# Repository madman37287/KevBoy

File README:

What is the KevBoy?

In its current state, the KevBoy is a breadboard prototype of a handheld RPI based retro gaming system using the retropie image.
ADD IMAGE

The KevBoy is a 

What is the purpose of making this public git repository?

1. Back-up data.  This project already had to be re-designed from scratch once in the past due to a laptop harddrive failure.  
2. Some SW and HW lack a large number of examples or documentation on the web. I hope this repository and documentation can assist with someone else's learning.
3. Method of showing off the project to any interested parties.

What has already been implemented within the KevBoy?

As previously mentioned, the KevBoy currently has a breadboard prototype shown in the image below.
ADD IMAGE

The breadboard design has 3 visible layers to it.  In the bottom layer, we have the controls.
These controls match what you would expect from a standard controller:
* D-Pad on the far left
* A, B, X, Y buttons on the far right
* Two analog sticks
* select (left) and start (right) buttons in between the analog sticks.

INSERT DIAGRAM

There is also an MCP3008 ADC between the analog sticks that convert the analog voltage outputted from the x and y axis potentiometers into a digital code readable by the PI.

The layer above the controls lives the necessary electrical components needed to connect the controls to the GPIO pins.  
In this layer we have LEDs acting only as Diodes.  These diodes are necessary due to the button matrix solution used to reduce the number of GPIO pins used from 16 to 8.
Without the diodes, multiple button presses can lead to an unpressed button being incorrectly registered (see below)

INSERT DIAGRAM

In its current prototype state, the PI currently has 11 connected buttons (including L3 on the DS3 analog), while the final will support at least 16 when adding R3 and the Triggers.
With several other devices needing to be connected to the GPIO pins, such as ADC, PWM speakers, UPS UART connections, ect, there are simply not enough pins.
The HW/SW solution was to build a button matrix, in which 16 buttons could be supported with 8 pins.

What still needs to be implemented?

* Upgrade to RPI5 (expecting CM5 to release later this year. CM4 to CM5 will not require PCB changes)
* Battery solution for RPI5 (5V 5A max compared to RPI4 5V 3A)
* PCB updates & PCB prototype
* 3D printable model for casing
* digitally controllable potentiometers for volume control
* code to support WIFI and Bluetooth status display. Perhaps also an airplane mode.
* Unit cooling

Setup:

Sound:
https://learn.adafruit.com/adafruit-max98357-i2s-class-d-mono-amp/raspberry-pi-usage

Background music: 
https://github.com/Naprosnia/RetroPie_BGM_Player

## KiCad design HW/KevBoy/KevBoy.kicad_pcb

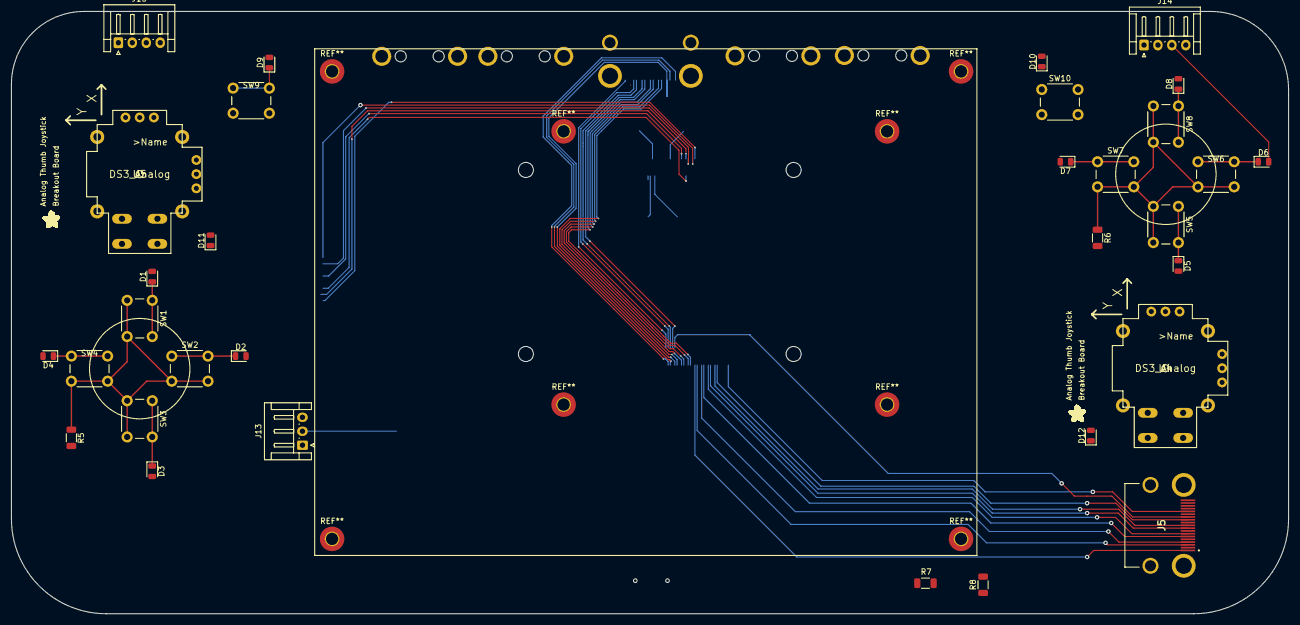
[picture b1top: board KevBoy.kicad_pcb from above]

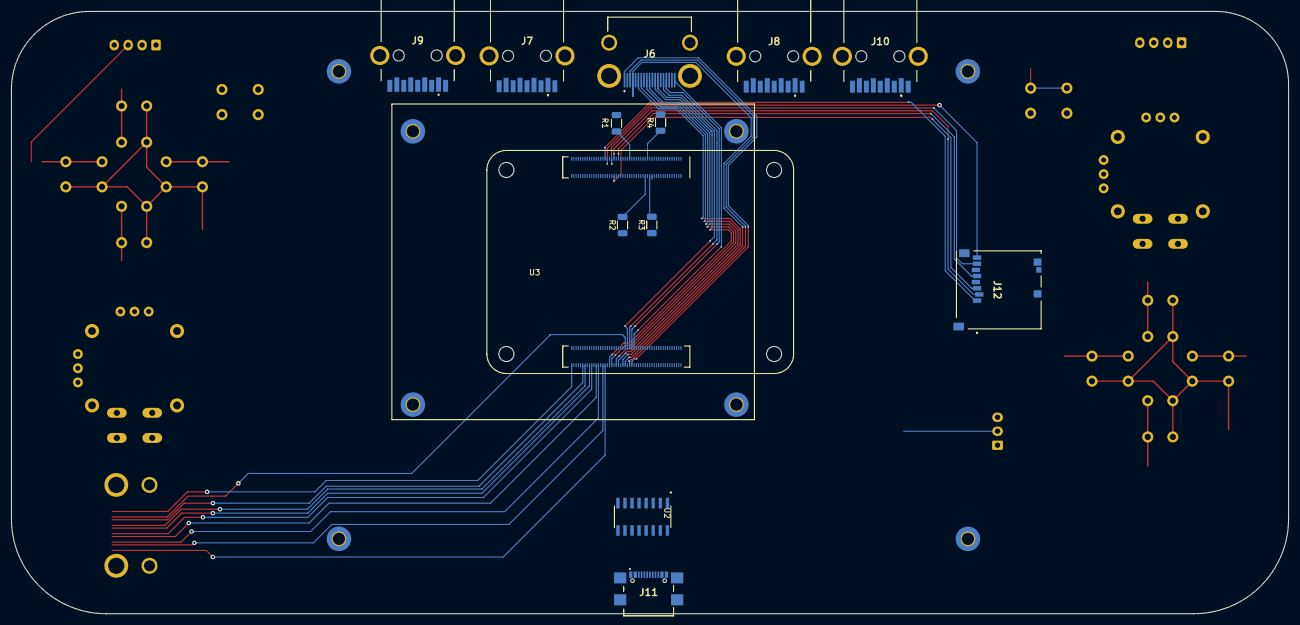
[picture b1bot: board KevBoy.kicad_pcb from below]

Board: 2 copper layers, 229.0 x 108.0 mm, 47 parts (13 on the bottom side), 58 nets.

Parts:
D1, D2, D3, D4, D5, D6, D7, D8, D9, D10, D11, D12: DIODE; D_0805_2012Metric
J5, J6: 208658-1051; 2086581051
J7, J8, J9, J10: 692122030100
J11: USB4110-GF-A; USB4110GFA
J12: MEM2051-00-195-00-A; MEM20510019500A
J13: Conn_01x03; JST_EH_S3B-EH_1x03_P2.50mm_Horizontal
J14, J15: Conn_01x04; JST_EH_S4B-EH_1x04_P2.50mm_Horizontal
R1, R2, R3, R4: 470; R_1206_3216Metric
R5, R6, R7, R8: 10k; R_1206_3216Metric
SW1, SW2, SW3, SW4, SW5, SW6, SW7, SW8, SW9, SW10: SW_Push; SW_PUSH_6mm_H7.3mm
U2: MCP3008; SOIC127P600X175-16N
U3: cm4conn; Raspberry-Pi-4-Compute-Module
U4, U5: DS3_Analog; JOYSTICK
U$1, U$1#2: ADAFRUIT200MIL

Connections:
5V: J13.1, U3.77, U3.79, U3.81, U3.83, U3.85, U3.87
ChargerInput: J11.A4, J11.A9, J11.B4, J11.B9
GND: J11.A1, J11.A12, J11.B1, J11.B12, J12.P6 (VSS), J13.3, R5.2, R6.2, R7.2, R8.2, U2.9 (DGND), U2.14 (AGND), U3.1, U3.2, U3.7, U3.8, U3.13, U3.14, U3.22, U3.23, U3.32, U3.33, U3.42, U3.43, U3.52, U3.53, U3.59, U3.60, U3.65, U3.66, U3.71, U3.74, U3.98, U3.107, U3.108, U3.113, U3.114, U3.119, U3.120, U3.125, U3.126, U3.131, U3.132, U3.137, U3.138, U3.144, U3.150, U3.155, U3.156, U3.161, U3.162, U3.167, U3.168, U3.173, U3.174, U3.179, U3.180, U3.185, U3.186, U3.191, U3.192, U3.197, U3.198
unnamed: D1.1 (K), SW1.1
unnamed: D1.2 (A), D5.2 (A), D9.2 (A), J14.2, R1.1
unnamed: D2.1 (K), SW2.1
unnamed: D3.1 (K), SW3.1
unnamed: D4.1 (K), SW4.1
unnamed: D5.1 (K), SW5.1
unnamed: D6.1 (K), SW6.1
unnamed: D7.1 (K), SW7.1
unnamed: D8.1 (K), SW8.1
unnamed: D9.1 (K), SW9.1
unnamed: D10.1 (K), SW10.1
unnamed: D2.2 (A), D6.2 (A), D10.2 (A), J14.3, R2.1
unnamed: D3.2 (A), D7.2 (A), D11.2 (A), J15.2, R3.1
unnamed: D4.2 (A), D8.2 (A), D12.2 (A), J15.3, R4.1
unnamed: J5.1, U3.170
unnamed: J5.3, U3.172
unnamed: J5.4, U3.176
unnamed: J5.6, U3.178
unnamed: J5.7, U3.182
unnamed: J5.9, U3.184
unnamed: J5.10, U3.188
unnamed: J5.12, U3.190
unnamed: J5.13, U3.151
unnamed: J5.15, U3.200
unnamed: J5.16, U3.199
unnamed: J5.19, U3.153
unnamed: J6.1, U3.146
unnamed: J6.3, U3.148
unnamed: J6.4, U3.152
unnamed: J6.6, U3.154
unnamed: J6.7, U3.158
unnamed: J6.9, U3.160
unnamed: J6.10, U3.164
unnamed: J6.12, U3.166
unnamed: J6.13, U3.149
unnamed: J6.15, U3.147
unnamed: J6.16, U3.145
unnamed: J6.19, U3.143
unnamed: J12.P1 (DAT2), U3.69
unnamed: J12.P2 (CD/DAT3), U3.61
unnamed: J12.P3 (CMD), U3.62
unnamed: J12.P5 (CLK), U3.57
unnamed: J12.P7 (DAT0), U3.63
unnamed: J12.P8 (DAT1), U3.67
unnamed: J13.2, U3.28
unnamed: J14.4, J15.1
unnamed: J15.4, R8.1
unnamed: R1.2, U3.47
unnamed: R2.2, U3.34
unnamed: R3.2, U3.30
unnamed: R4.2, U3.31
unnamed: R5.1, SW1.2, SW2.2, SW3.2, SW4.2, U3.50
unnamed: R6.1, SW5.2, SW6.2, SW7.2, SW8.2, U3.48
unnamed: R7.1, SW9.2, SW10.2, U3.46
unnamed: U2.15 (Vref), U2.16 (Vdd)

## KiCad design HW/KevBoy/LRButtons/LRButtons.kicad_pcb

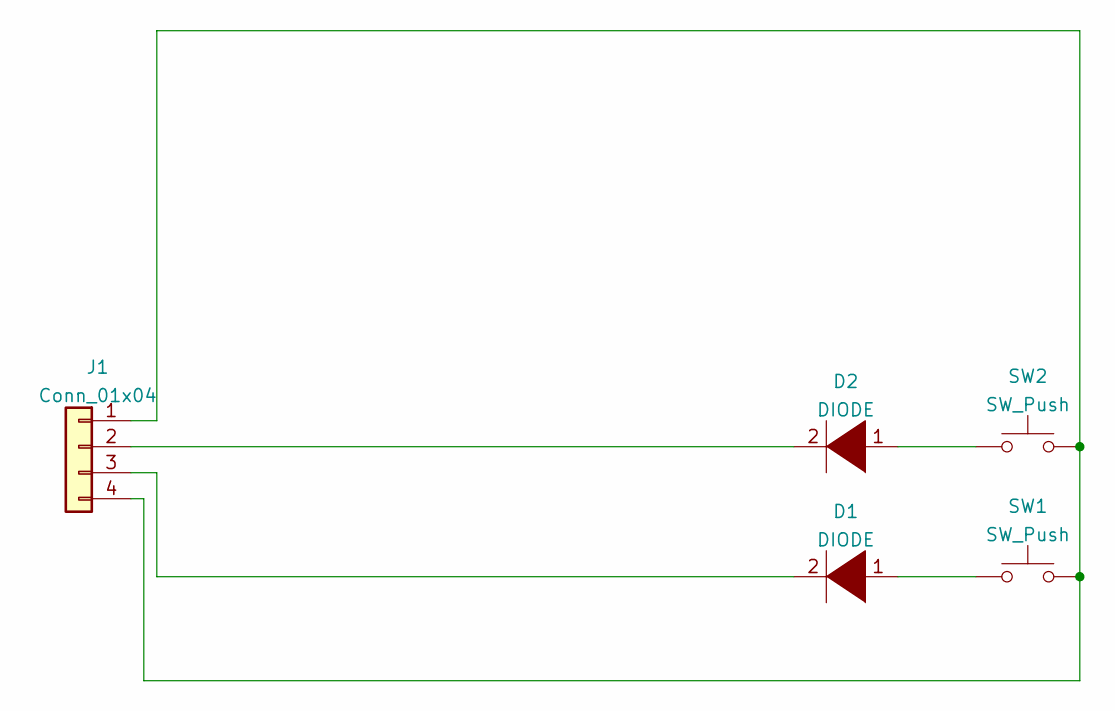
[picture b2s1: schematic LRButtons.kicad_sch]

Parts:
D1, D2: DIODE; D_0805_2012Metric
J1: Conn_01x04; JST_EH_B4B-EH-A_1x04_P2.50mm_Vertical
SW1, SW2: SW_Push; SW_PUSH_6mm_H7.3mm

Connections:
unnamed: D1.2 (A), J1.3
unnamed: D2.2 (A), J1.2
unnamed: J1.1, J1.4, SW1.2, SW2.2
unnamed: D1.1 (K), SW1.1
unnamed: D2.1 (K), SW2.1

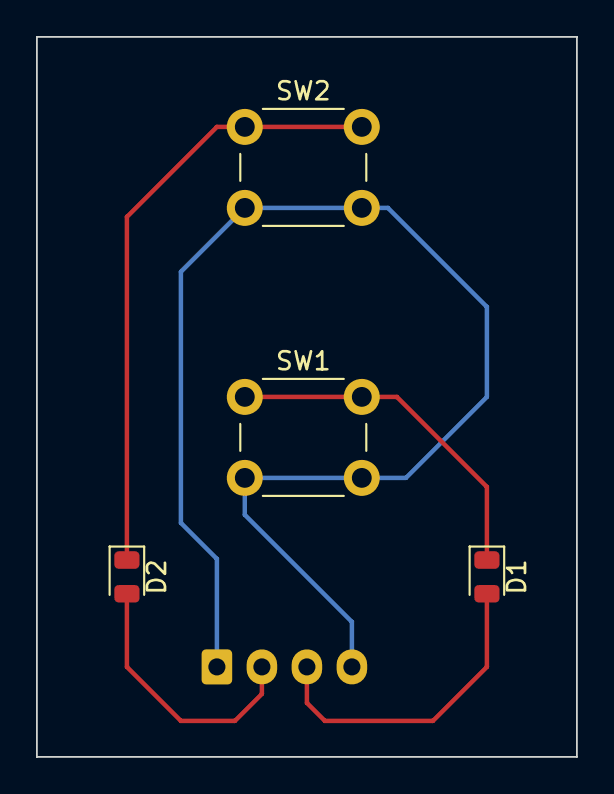
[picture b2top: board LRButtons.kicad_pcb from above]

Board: 2 copper layers, 30.0 x 40.0 mm, 5 parts (1 on the bottom side), 5 nets.

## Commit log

2024-05-30 Create README
    initial but unfinished README
2024-05-30 initial file push
2024-06-06 Files necessary for pi5 integration
2024-06-07 code to support l and r buttons
2024-06-10 Update README
    added link for I2S setup
2024-06-10 Update README
    link to background music instructions
